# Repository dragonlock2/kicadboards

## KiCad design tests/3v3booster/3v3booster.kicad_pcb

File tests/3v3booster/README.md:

# 3v3booster

Designed June 2019

https://matthewtran.dev/2019/06/tps61201-3-3v-booster/

The board that led me to realize that there are specialized chips for most applications. Board is designed for the adjustable version but the one I had was the fixed one so the board as-is doesn't work.

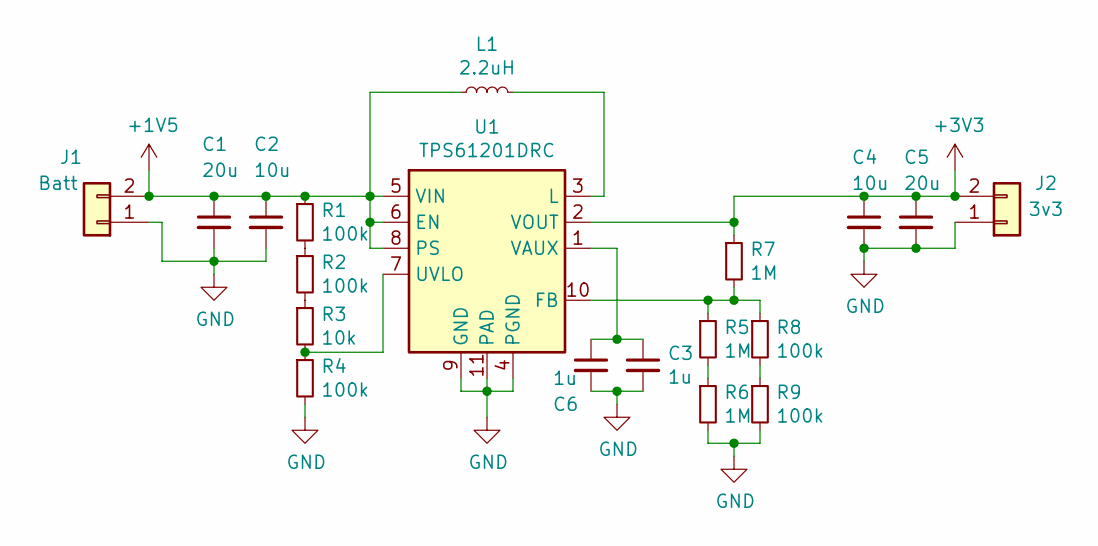
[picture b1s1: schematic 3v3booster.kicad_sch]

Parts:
C1, C5: 20u; C_0603_1608Metric_Pad1.05x0.95mm_HandSolder
C2, C4: 10u; C_0402_1005Metric
C3, C6: 1u; C_0201_0603Metric
J1: Batt; PinHeader_1x02_P2.54mm_Vertical
J2: 3v3; PinHeader_1x02_P2.54mm_Vertical
L1: 2.2uH; L_Abracon_ASPI-3012S
R1, R2, R4, R8, R9: 100k; R_0603_1608Metric_Pad1.05x0.95mm_HandSolder
R3: 10k; R_0603_1608Metric_Pad1.05x0.95mm_HandSolder
R5, R6, R7: 1M; R_0603_1608Metric_Pad1.05x0.95mm_HandSolder
U1: TPS61201DRC; Texas_S-PVSON-N10_ThermalVias

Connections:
+1V5: C1.1, C2.1, J1.2, L1.1, R1.1, U1.5 (VIN), U1.6 (EN), U1.8 (PS)
+3V3: C4.1, C5.1, J2.2, R7.1, U1.2 (VOUT)
GND: C1.2, C2.2, C3.2, C4.2, C5.2, C6.2, J1.1, J2.1, R4.2, R6.2, R9.2, U1.4 (PGND), U1.9 (GND), U1.11 (PAD)
unnamed: C3.1, C6.1, U1.1 (VAUX)
unnamed: L1.2, U1.3 (L)
unnamed: R1.2, R2.1
unnamed: R2.2, R3.1
unnamed: R3.2, R4.1, U1.7 (UVLO)
unnamed: R5.1, R7.2, R8.1, U1.10 (FB)
unnamed: R5.2, R6.1
unnamed: R8.2, R9.1

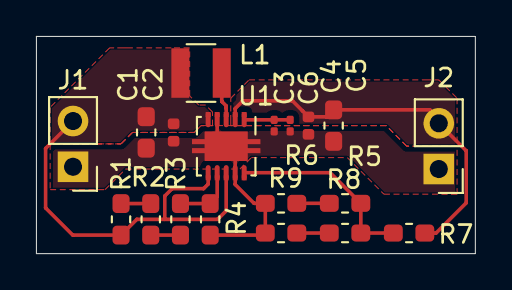
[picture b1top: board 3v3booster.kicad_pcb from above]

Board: 2 copper layers, 24.4 x 12.1 mm, 19 parts (0 on the bottom side), 11 nets.

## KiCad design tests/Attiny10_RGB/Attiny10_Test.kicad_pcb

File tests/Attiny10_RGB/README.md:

# Attiny10_RGB

Designed January 2020

https://matthewtran.dev/2020/01/attiny10-tiny-low-cost-mcu/

A USB powered ATtiny10 with RGB LED.

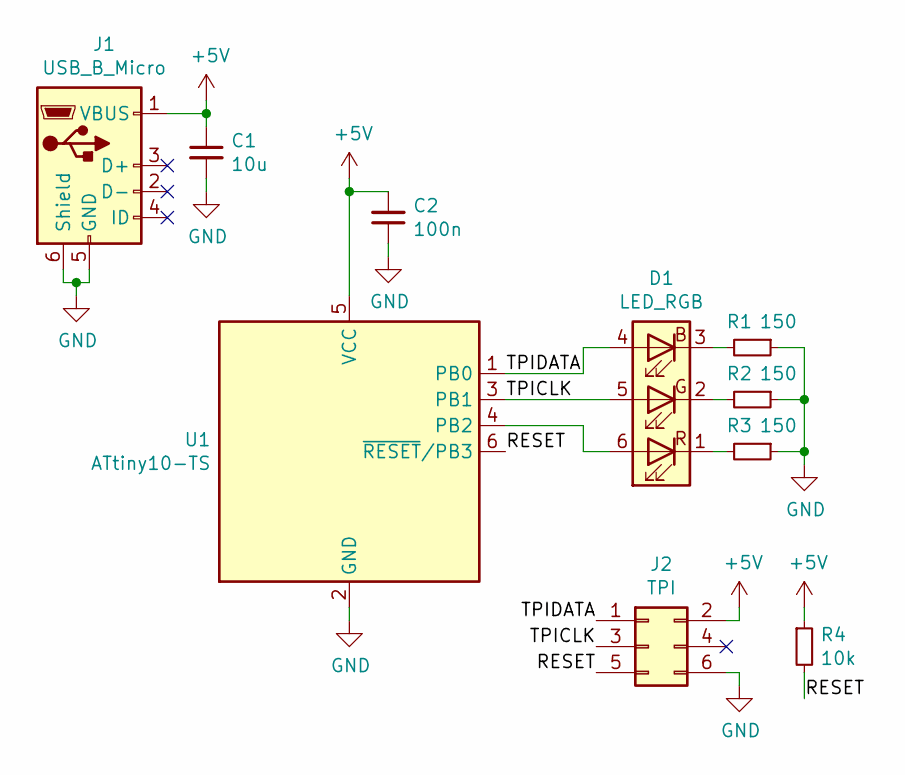
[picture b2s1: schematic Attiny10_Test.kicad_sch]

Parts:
C1: 10u; C_0805_2012Metric
C2: 100n; C_0603_1608Metric
D1: LED_RGB; LED_RGB_5050-6
J1: USB_B_Micro; USB_Micro-B_Amphenol_10103594-0001LF_Horizontal
J2: TPI; PinHeader_2x03_P2.54mm_Vertical
R1, R2, R3: 150; R_0603_1608Metric
R4: 10k; R_0603_1608Metric
U1: ATtiny10-TS; SOT-23-6

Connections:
+5V: C1.1, C2.2, J1.1 (VBUS), J2.2, R4.1, U1.5 (VCC)
/RESET: J2.5, R4.2, U1.6 (~RESET/PB3)
/TPICLK: D1.5 (GA), J2.3, U1.3 (PB1)
/TPIDATA: D1.4 (BA), J2.1, U1.1 (PB0)
GND: C1.2, C2.1, J1.5 (GND), J1.6 (Shield), J2.6, R1.1, R2.1, R3.1, U1.2 (GND)
unnamed: D1.1 (RK), R3.2
unnamed: D1.2 (GK), R2.2
unnamed: D1.3 (BK), R1.2
unnamed: D1.6 (RA), U1.4 (PB2)

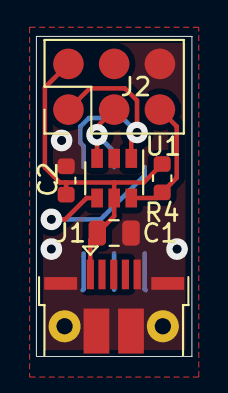
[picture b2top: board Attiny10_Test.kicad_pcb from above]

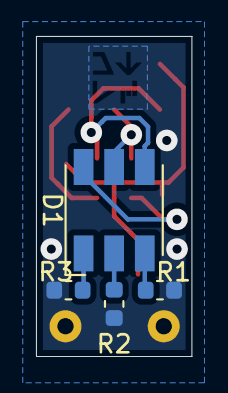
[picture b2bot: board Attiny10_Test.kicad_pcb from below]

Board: 2 copper layers, 8.6 x 17.8 mm, 10 parts (4 on the bottom side), 9 nets.

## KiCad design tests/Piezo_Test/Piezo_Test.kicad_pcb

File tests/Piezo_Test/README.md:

# Piezo_Test

Designed August 2019

Amplifier for a piezo element. Didn't work very well.

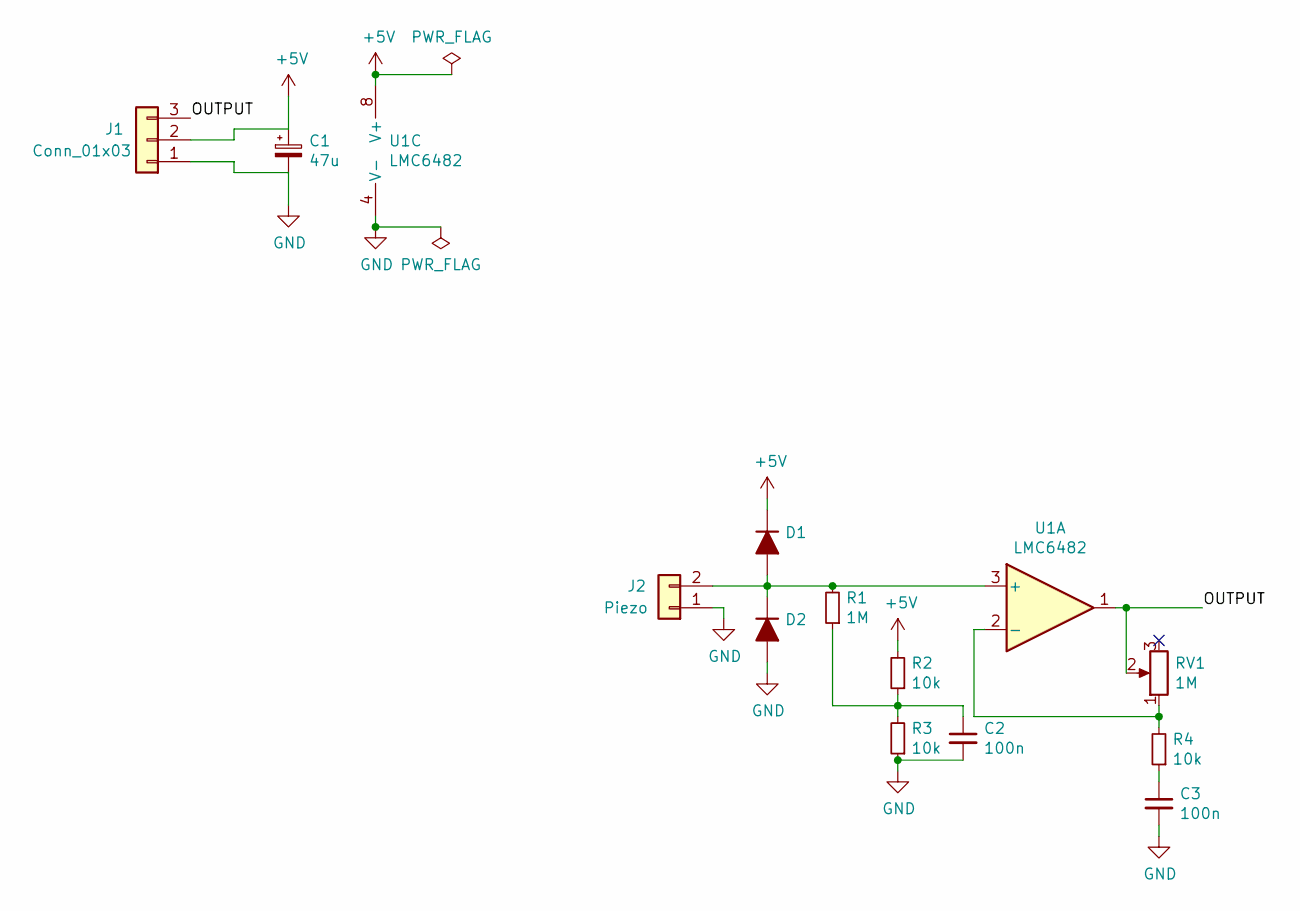
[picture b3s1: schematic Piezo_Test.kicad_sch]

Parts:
C1: 47u; CP_Elec_6.3x5.4
C2, C3: 100n; C_0805_2012Metric_Pad1.15x1.40mm_HandSolder
D1, D2: D_MiniMELF
J1: Conn_01x03; PinHeader_1x03_P2.54mm_Vertical
J2: Piezo; PinHeader_1x02_P2.54mm_Vertical
R1: 1M; R_0603_1608Metric
R2, R3, R4: 10k; R_0603_1608Metric
RV1: 1M; Potentiometer_Runtron_RM-065_Vertical
U1: LMC6482; SMDIP-8_W9.53mm

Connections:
+5V: C1.1, D1.1 (K), J1.2, R2.2, U1.8 (V+)
/OUTPUT: J1.3, RV1.2, U1.1
GND: C1.2, C2.2, C3.2, D2.2 (A), J1.1, J2.1, R3.1, U1.4 (V-)
unnamed: C2.1, R1.1, R2.1, R3.2
unnamed: C3.1, R4.1
unnamed: D1.2 (A), D2.1 (K), J2.2, R1.2, U1.3 (+)
unnamed: R4.2, RV1.1, U1.2 (-)

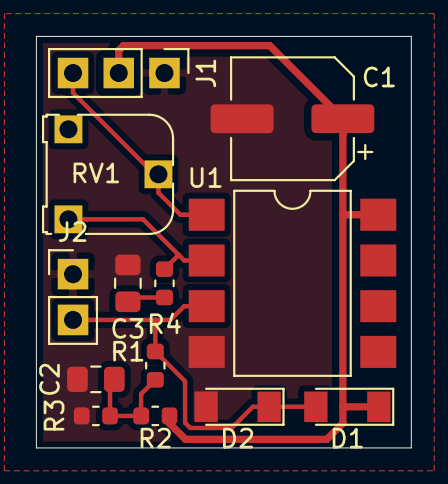
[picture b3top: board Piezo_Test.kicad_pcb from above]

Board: 2 copper layers, 20.8 x 22.9 mm, 13 parts (0 on the bottom side), 7 nets.

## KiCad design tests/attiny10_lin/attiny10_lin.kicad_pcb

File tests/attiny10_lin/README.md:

# attiny10_lin

Attempt at a cheap bit-banged LIN node using an ATtiny10.

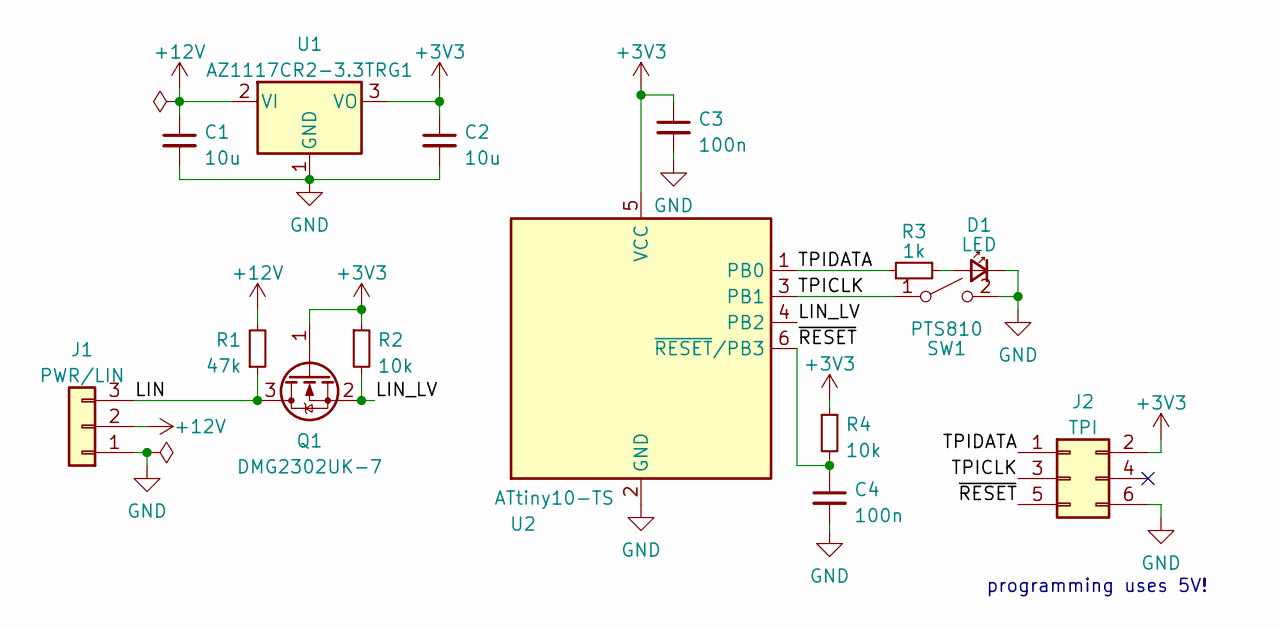
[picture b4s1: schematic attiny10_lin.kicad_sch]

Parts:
C1, C2: 10u; C_0805_2012Metric
C3, C4: 100n; C_0603_1608Metric
D1: LED; LED_0603_1608Metric
J1: PWR/LIN; PinHeader_1x03_P2.54mm_Vertical
J2: TPI; Tag-Connect_TC2030-IDC-NL_2x03_P1.27mm_Vertical
Q1: DMG2302UK-7; SOT-23
R1: 47k; R_0603_1608Metric
R2, R4: 10k; R_0603_1608Metric
R3: 1k; R_0603_1608Metric
SW1: PTS810; SW_SPST_PTS810
U1: AZ1117CR2-3.3TRG1; SOT-89-3
U2: ATtiny10-TS; SOT-23-6

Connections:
+3V3: C2.1, C3.1, J2.2, Q1.1 (G), R2.1, R4.1, U1.3 (VO), U2.5 (VCC)
+12V: C1.1, J1.2, R1.2, U1.2 (VI)
/LIN: J1.3, Q1.3 (D), R1.1
/LIN_LV: Q1.2 (S), R2.2, U2.4 (PB2)
/TPICLK: J2.3, SW1.1 (A), U2.3 (PB1)
/TPIDATA: J2.1, R3.1, U2.1 (PB0)
/~RESET: C4.1, J2.5, R4.2, U2.6 (~RESET/PB3)
GND: C1.2, C2.2, C3.2, C4.2, D1.1 (K), J1.1, J2.6, SW1.2 (B), U1.1 (GND), U2.2 (GND)
unnamed: D1.2 (A), R3.2

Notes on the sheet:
programming uses 5V!

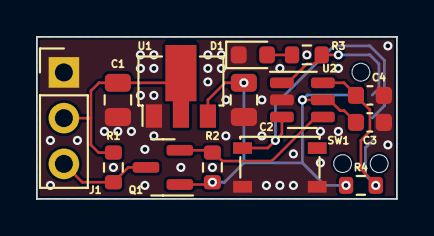
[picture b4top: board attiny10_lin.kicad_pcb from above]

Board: 2 copper layers, 20.0 x 9.0 mm, 15 parts (1 on the bottom side), 9 nets.

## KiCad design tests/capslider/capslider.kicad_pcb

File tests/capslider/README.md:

# capslider

Designed April 2020

https://matthewtran.dev/2021/01/tinkering-with-qtouch/

Test for capacitive touch slider with split end contact (making it a wheel!). Designed in KiCad 5 before hatched pours became a thing so there was a hacky workaround using DipTrace.

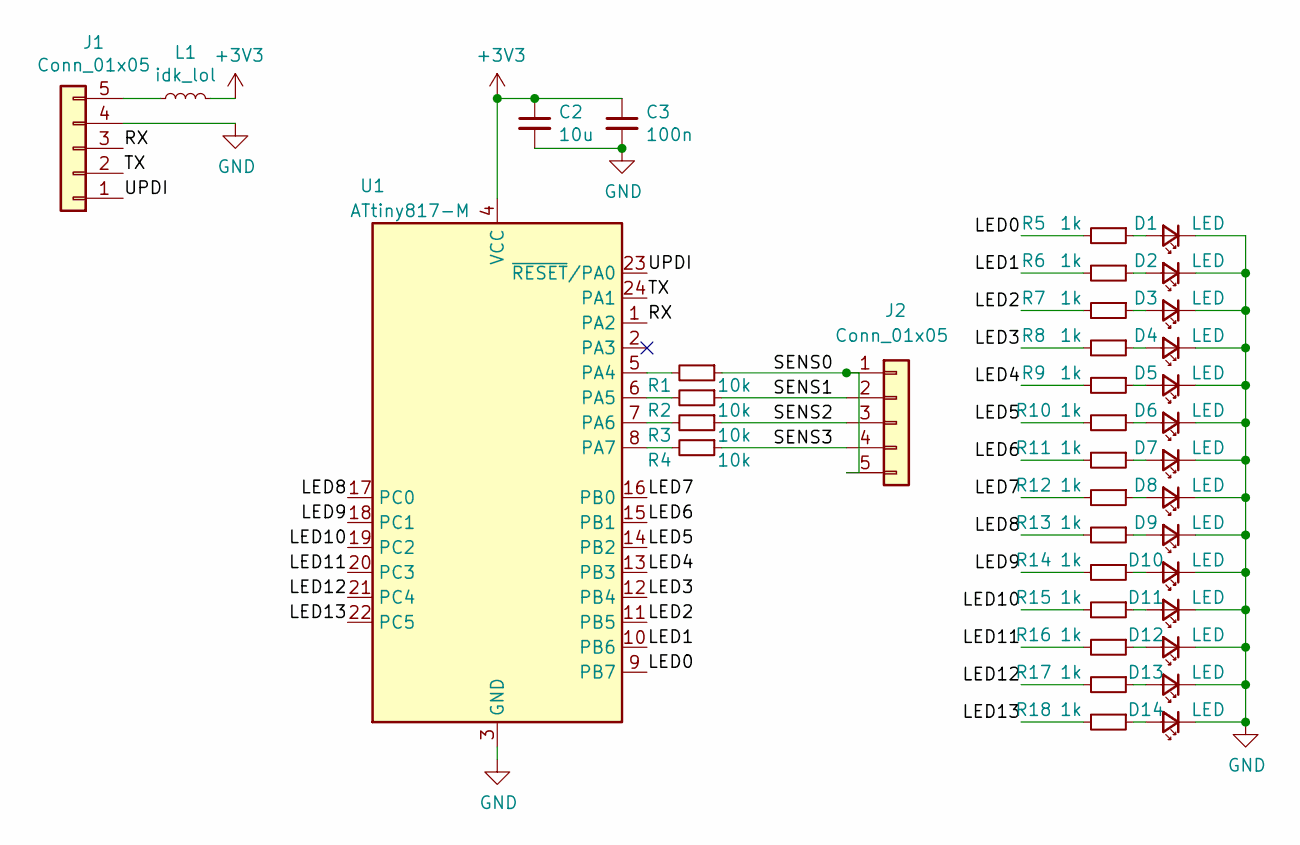
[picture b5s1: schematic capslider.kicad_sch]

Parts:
C2: 10u; C_0805_2012Metric
C3: 100n; C_0805_2012Metric
D1, D2, D3, D4, D5, D6, D7, D8, D9, D10, D11, D12, D13, D14: LED; LED_0603_1608Metric
J1: Conn_01x05; PinHeader_1x05_P2.54mm_Vertical
J2: Conn_01x05; slider
L1: idk_lol; L_1206_3216Metric
R1, R2, R3, R4: 10k; R_0603_1608Metric
R5, R6, R7, R8, R9, R10, R11, R12, R13, R14, R15, R16, R17, R18: 1k; R_0603_1608Metric
U1: ATtiny817-M; QFN-24-1EP_4x4mm_P0.5mm_EP2.6x2.6mm

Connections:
+3V3: C2.1, C3.1, L1.2, U1.4 (VCC)
/LED0: R5.2, U1.9 (PB7)
/LED1: R6.2, U1.10 (PB6)
/LED2: R7.2, U1.11 (PB5)
/LED3: R8.2, U1.12 (PB4)
/LED4: R9.2, U1.13 (PB3)
/LED5: R10.2, U1.14 (PB2)
/LED6: R11.2, U1.15 (PB1)
/LED7: R12.2, U1.16 (PB0)
/LED8: R13.2, U1.17 (PC0)
/LED9: R14.2, U1.18 (PC1)
/LED10: R15.2, U1.19 (PC2)
/LED11: R16.2, U1.20 (PC3)
/LED12: R17.2, U1.21 (PC4)
/LED13: R18.2, U1.22 (PC5)
/RX: J1.3, U1.1 (PA2)
/SENS0: J2.1, J2.5, R1.1
/SENS1: J2.2, R2.1
/SENS2: J2.3, R3.1
/SENS3: J2.4, R4.1
/TX: J1.2, U1.24 (PA1)
/UPDI: J1.1, U1.23 (~RESET/PA0)
GND: C2.2, C3.2, D1.1 (K), D2.1 (K), D3.1 (K), D4.1 (K), D5.1 (K), D6.1 (K), D7.1 (K), D8.1 (K), D9.1 (K), D10.1 (K), D11.1 (K), D12.1 (K), D13.1 (K), D14.1 (K), J1.4, U1.3 (GND), U1.25 (GND)
unnamed: D1.2 (A), R5.1
unnamed: D2.2 (A), R6.1
unnamed: D3.2 (A), R7.1
unnamed: D4.2 (A), R8.1
unnamed: D5.2 (A), R9.1
unnamed: D6.2 (A), R10.1
unnamed: D7.2 (A), R11.1
unnamed: D8.2 (A), R12.1
unnamed: D9.2 (A), R13.1
unnamed: D10.2 (A), R14.1
unnamed: D11.2 (A), R15.1
unnamed: D12.2 (A), R16.1
unnamed: D13.2 (A), R17.1
unnamed: D14.2 (A), R18.1
unnamed: J1.5, L1.1
unnamed: R1.2, U1.5 (PA4)
unnamed: R2.2, U1.6 (PA5)
unnamed: R3.2, U1.7 (PA6)
unnamed: R4.2, U1.8 (PA7)

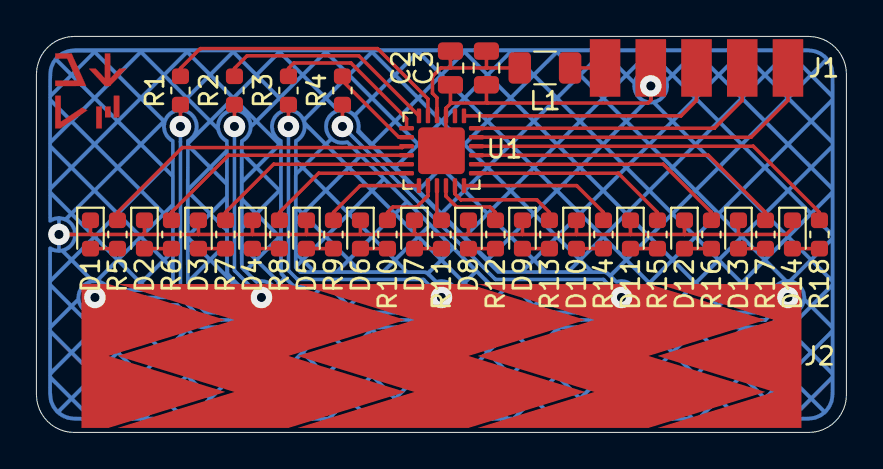
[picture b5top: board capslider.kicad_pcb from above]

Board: 2 copper layers, 45.0 x 22.0 mm, 38 parts (0 on the bottom side), 42 nets.

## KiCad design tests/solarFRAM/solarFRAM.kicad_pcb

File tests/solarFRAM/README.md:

# solarFRAM

Harnessing the power of the sun to test the endurance of FRAM.

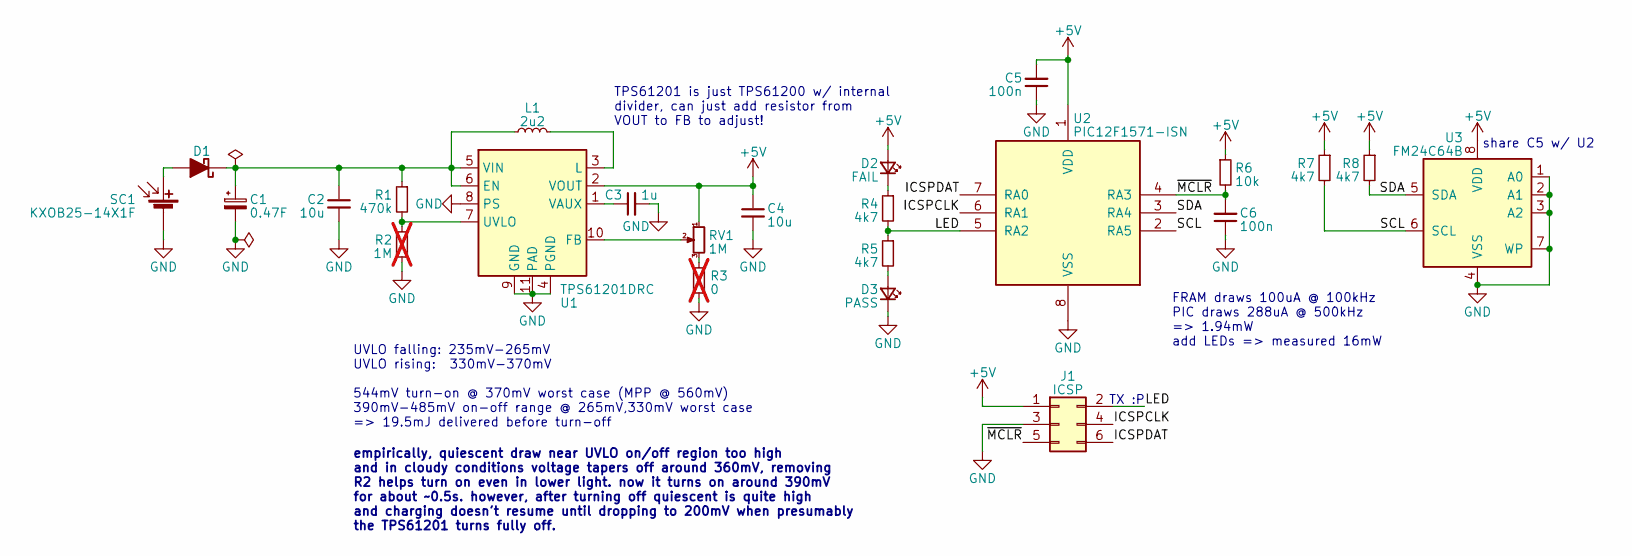
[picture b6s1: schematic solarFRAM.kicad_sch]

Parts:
C1: 0.47F; PinHeader_1x02_P2.54mm_Vertical
C2, C4: 10u; C_0603_1608Metric
C3: 1u; C_0603_1608Metric
C5, C6: 100n; C_0603_1608Metric
D1: D_Schottky_Filled; D_SOD-123
D2: FAIL; LED_0603_1608Metric
D3: PASS; LED_0603_1608Metric
J1: ICSP; Tag-Connect_TC2030-IDC-NL_2x03_P1.27mm_Vertical
L1: 2u2; L_0805_2012Metric
R1: 470k; R_0603_1608Metric
R2: 1M; R_0603_1608Metric; not fitted
R3: 0; R_0603_1608Metric; not fitted
R4, R5, R7, R8: 4k7; R_0603_1608Metric
R6: 10k; R_0603_1608Metric
RV1: 1M; Potentiometer_Bourns_TC33X_Vertical
SC1: KXOB25-14X1F; R_4020_10251Metric
U1: TPS61201DRC; Texas_S-PVSON-N10_ThermalVias
U2: PIC12F1571-ISN; SOIC-8_3.9x4.9mm_P1.27mm
U3: FM24C64B; SOIC-8_3.9x4.9mm_P1.27mm

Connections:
+5V: C4.1, C5.2, D2.2 (A), J1.1, R6.1, R7.1, R8.1, RV1.1, U1.2 (VOUT), U2.1 (VDD), U3.8 (VDD)
/ICSPCLK: J1.4, U2.6 (RA1)
/ICSPDAT: J1.6, U2.7 (RA0)
/LED: J1.2, R4.2, R5.1, U2.5 (RA2)
/SCL: R7.2, U2.2 (RA5), U3.6 (SCL)
/SDA: R8.2, U2.3 (RA4), U3.5 (SDA)
/~MCLR: C6.2, J1.5, R6.2, U2.4 (RA3)
GND: C1.2, C2.2, C3.2, C4.2, C5.1, C6.1, D3.1 (K), J1.3, R2.2, R3.2, SC1.2 (-), U1.4 (PGND), U1.8 (PS), U1.9 (GND), U1.11 (PAD), U2.8 (VSS), U3.1 (A0), U3.2 (A1), U3.3 (A2), U3.4 (VSS), U3.7 (WP)
unnamed: C1.1, C2.1, D1.1 (K), L1.1, R1.1, U1.5 (VIN), U1.6 (EN)
unnamed: D1.2 (A), SC1.1 (+)
unnamed: D2.1 (K), R4.1
unnamed: D3.2 (A), R5.2
unnamed: R3.1, RV1.3
unnamed: RV1.2, U1.10 (FB)
unnamed: L1.2, U1.3 (L)
unnamed: R1.2, R2.1, U1.7 (UVLO)
unnamed: C3.1, U1.1 (VAUX)

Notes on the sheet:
TX :P
TPS61201 is just TPS61200 w/ internal divider, can just add resistor from VOUT to FB to adjust!
empirically, quiescent draw near UVLO on/off region too high and in cloudy conditions voltage tapers off around 360mV, removing R2 helps turn on even in lower light. now it turns on around 390mV for about ~0.5s. however, after turning off quiescent is quite high and charging doesn't resume until dr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
share C5 w/ U2
FRAM draws 100uA @ 100kHz PIC draws 288uA @ 500kHz => 1.94mW add LEDs => measured 16mW
UVLO falling: 235mV-265mV UVLO rising: 330mV-370mV 544mV turn-on @ 370mV worst case (MPP @ 560mV) 390mV-485mV on-off range @ 265mV,330mV worst case => 19.5mJ delivered before turn-off

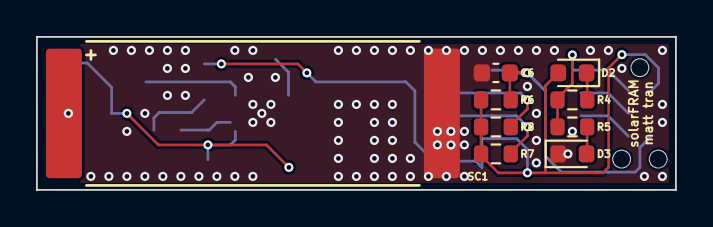
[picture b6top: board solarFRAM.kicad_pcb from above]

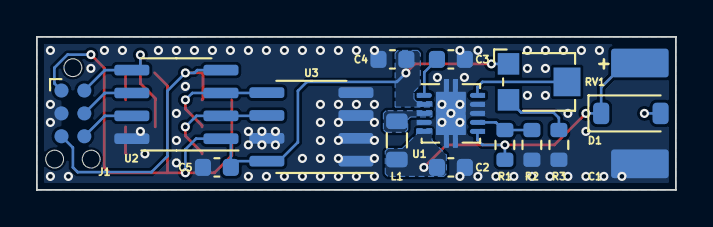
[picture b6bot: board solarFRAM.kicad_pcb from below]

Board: 2 copper layers, 35.5 x 8.5 mm, 24 parts (15 on the bottom side), 17 nets.

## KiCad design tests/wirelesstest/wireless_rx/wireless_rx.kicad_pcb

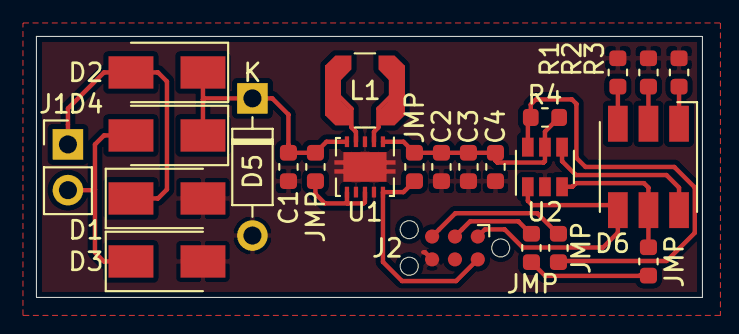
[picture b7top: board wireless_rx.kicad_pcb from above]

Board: 2 copper layers, 37.0 x 14.5 mm, 24 parts (0 on the bottom side), 14 nets.

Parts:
C1, C2, C3: 10u; C_0603_1608Metric
C4: 100n; C_0603_1608Metric
D1, D2, D3, D4: LL4007?; D_SMA
D5: 5.6v; D_DO-35_SOD27_P7.62mm_Horizontal
D6: LED_RGB; LED_RGB_5050-6
J1: Coil; PinHeader_1x02_P2.54mm_Vertical
J2: TPI; Tag-Connect_TC2030-IDC-NL_2x03_P1.27mm_Vertical
JMP: R_0603_1608Metric
JMP#2, JMP#3, JMP#4, JMP#5: R_0603_1608Metric
L1: 2.2u; L_Coilcraft_LPS4018
R1, R2, R3: 50; R_0603_1608Metric
R4: 10k; R_0603_1608Metric
U1: TPS63001; Texas_DRC0010J_ThermalVias
U2: ATtiny10-TS; SOT-23-6

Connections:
+3V3: C2.1, C3.1, C4.1, J2.2, JMP#2.1, JMP#2.2, R4.1, U1.1, U1.10, U2.5
/RST: J2.5, JMP#4.1, JMP#4.2, R4.2, U2.6
/TPI_CLK: D6.5, J2.3, JMP#3.1, JMP#3.2, JMP#5.1, JMP#5.2, U2.3
/TPI_DATA: D6.4, J2.1, U2.1
GND: C1.2, C2.2, C3.2, C4.2, D3.2, D4.2, D5.2, J2.6, R1.1, R2.1, R3.1, U1.3, U1.7, U1.9, U1.11, U2.2
unnamed: C1.1, D1.1, D2.1, D5.1, JMP.1, JMP.2, U1.5, U1.6, U1.8
unnamed: D1.2, D3.1, J1.2
unnamed: D2.2, D4.1, J1.1
unnamed: D6.1, R3.2
unnamed: D6.2, R2.2
unnamed: D6.3, R1.2
unnamed: D6.6, U2.4
unnamed: L1.1, U1.4
unnamed: L1.2, U1.2
